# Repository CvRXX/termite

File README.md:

# Termite Devboard

Termite is an open source hardware devboard aimed at embedded library developers.

## Features
  * An stm32f103 cortex m3 microcontroller.
  * A protoboard space to mount components on.
  * An RGB led.
  * Support for lithium ion batteries as power source.
  * Charging of lithium ion batteries.
  * 128Kb of external onboard flash memory

## The idea
The idea came from my teacher who is developing multiple embedded libraries.
These libraries have support for many different types of displays, sensors, etc.
Everytime a change is made to the library my teacher had to hookup the sensors to an devboard. 
His wish was to have a devboard cheap enough he could solder the components on and leave them on.
This is what termite was designed for.

## Power
The board can be powered by 5v or 3.3 volt. 
There is a usb connector which can be used for power as well. 
Another option is to connect a lithium ion battery. 
If there is a voltage on the 5v rail a connected battery will be charged.

### WARNINGS about battery usage: 
  1. Only connect lithium ion batteries with a voltage of 3.7V marked on them.
  2. Don't connect batteries with a capacity less than 250mAh.
  3. Only connect batteries with an integrated protection circuit.
  4. Don't charge your board unattended. 

### Status leds:

| Green led  | Red led | Meaning |
| ------------- | ------------- | ------------- |
| Off  | Off  | No external power connected.
| On  | Off  | External power connected, battery full or not connected.
| On  | On  | External power connected, battery charging
| On  | Blinking  | External power connected, issue with battery detected.

## Flashing the microcontroller
The board include an IDC header that matches the pinout of the stlink-v2.
You need an IDC cable to connect between the flash tool and the board. 
After that it flashes just as any other stm microcontroller.

## Opening the files
To open the design files you need kicad. 
It's free software so you can just download it.

## Producing a board
If you want to produce a board you can export all the needed files from kicad.
It is hard (read impossible) to solder the battery charging chip with a normal soldering iron.
So if you want the battery charging you need to arrange for better equipment or arrange for pick and placing the board.

The board is 4 layer and can be produced by almost every common pcb factory.

If there are any problems I'm happy to help you on your way.
Just contact me!

## Testing the board
After production a testing script is available to check if the board is functioning oke. 
You can find the script and it's docs [here](https://github.com/CvRXX/termite-test-firmware).

## Examples with the termite board.
  * [A temperature sensor for painting scouting boats.](https://github.com/CvRXX/termite-demo)

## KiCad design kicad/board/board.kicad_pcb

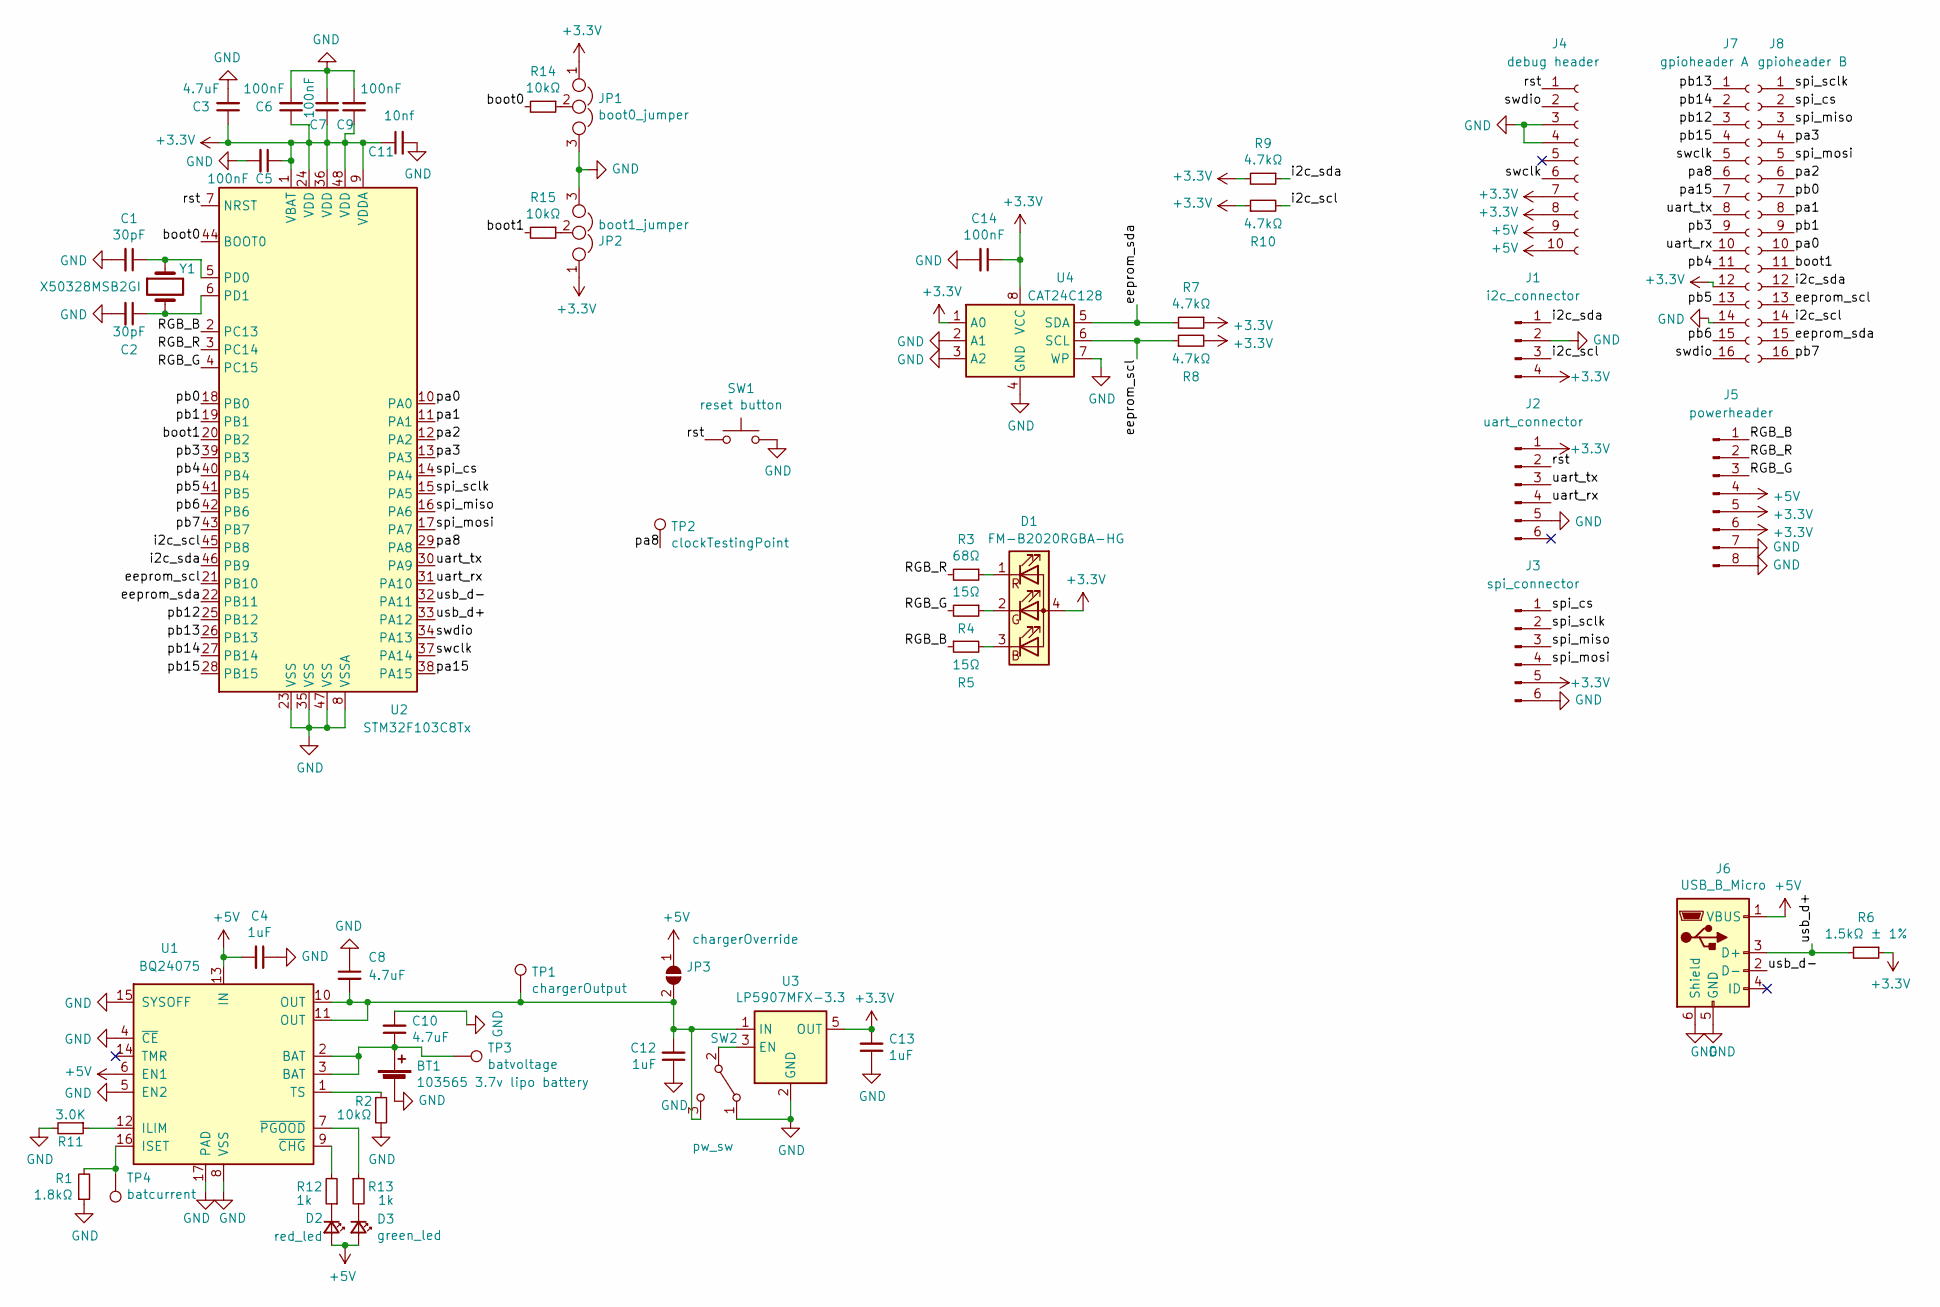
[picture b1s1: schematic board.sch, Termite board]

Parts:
BT1: 103565 3.7v lipo battery; PinHeader_1x02_P2.54mm_Vertical; LCSC C152154
C1, C2: 30pF; C_0402_1005Metric; LCSC C1570
C3, C8, C10: 4.7uF; C_0603_1608Metric; LCSC C19666
C4, C12, C13: 1uF; C_1206_3216Metric; LCSC C1848
C5, C6, C7, C9, C14: 100nF; C_0402_1005Metric; LCSC C1525
C11: 10nf; C_0603_1608Metric; LCSC C57112
D1: FM-B2020RGBA-HG; LCSC C108793
D2: red_led; LED_0603_1608Metric; LCSC C2286
D3: green_led; LED_0603_1608Metric; LCSC C72043
J1: i2c_connector; PinHeader_1x04_P2.54mm_Vertical; LCSC C124378
J2: uart_connector; PinSocket_1x06_P2.54mm_Horizontal; LCSC C225514
J3: spi_connector; PinHeader_1x06_P2.54mm_Vertical; LCSC C492405
J4: debug header; IDC-Header_2x05_P2.54mm_Vertical; LCSC C5665
J5: powerheader; PinHeader_1x08_P2.54mm_Vertical; LCSC C124381
J6: USB_B_Micro; AMPHENOL_10118194-0001LF; LCSC C132563
J7: gpioheader A; PinSocket_2x08_P2.54mm_Vertical
J8: gpioheader B; PinSocket_2x08_P2.54mm_Vertical
JP1: boot0_jumper; PinHeader_1x03_P2.54mm_Vertical; LCSC C49257
JP2: boot1_jumper; PinHeader_1x03_P2.54mm_Vertical; LCSC C49257
JP3: chargerOverride; SolderJumper-2_P1.3mm_Open_Pad1.0x1.5mm
R1: 1.8kΩ; R_0603_1608Metric_Pad0.98x0.95mm_HandSolder; LCSC C4177
R2, R14, R15: 10kΩ; R_0402_1005Metric; LCSC C25744
R3: 68Ω; R_0402_1005Metric; LCSC C25131
R4, R5: 15Ω; R_0402_1005Metric; LCSC C25083
R6: 1.5kΩ ± 1%; R_0402_1005Metric; LCSC C98835
R7, R8, R9, R10: 4.7kΩ; R_0402_1005Metric; LCSC C25900
R11: 3.0K; R_0603_1608Metric_Pad0.98x0.95mm_HandSolder; LCSC C4211
R12, R13: 1k; R_0402_1005Metric; LCSC C11702
SW1: reset button; K2-6639DP-E4SW-04; LCSC C223748
SW2: pw_sw; K301235D; LCSC C223839
TP1: chargerOutput; TestPoint_Pad_D1.0mm
TP2: clockTestingPoint; TestPoint_Pad_D1.0mm
TP3: batvoltage; TestPoint_Pad_D1.0mm
TP4: batcurrent; TestPoint_Pad_D1.0mm
U1: BQ24075; QFN-16-1EP_3x3mm_P0.5mm_EP1.7x1.7mm; LCSC C15464
U2: STM32F103C8Tx; LQFP-48_7x7mm_P0.5mm; LCSC C8304
U3: LP5907MFX-3.3; SOT-23-5; LCSC C80670
U4: CAT24C128; SOIC-8_3.9x4.9mm_P1.27mm; LCSC C81195
Y1: X50328MSB2GI; Crystal_SMD_5032-2Pin_5.0x3.2mm; LCSC C115962

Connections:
+3V3: C3.1, C5.1, C6.1, C7.1, C9.1, C11.1, C13.2, C14.1, D1.4 (A), J1.4, J2.1, J3.5, J4.7, J4.8, J5.5, J5.6, J7.12, JP1.1, JP2.1, R6.1, R7.1, R8.2, R9.2, R10.1, U2.1 (VBAT), U2.9 (VDDA), U2.24 (VDD), U2.36 (VDD), U2.48 (VDD), U3.5 (OUT), U4.1 (A0), U4.8 (VCC)
+5V: C4.2, D2.2 (A), D3.2 (A), J4.9, J4.10, J5.4, J6.1 (VBUS), JP3.1 (A), U1.6 (EN1), U1.13 (IN)
/RGB_B: J5.1, R5.1, U2.2 (PC13)
/RGB_G: J5.3, R4.2, U2.4 (PC15)
/RGB_R: J5.2, R3.2, U2.3 (PC14)
/boot0: R14.2, U2.44 (BOOT0)
/boot1: J8.11, R15.2, U2.20 (PB2)
/eeprom_scl: J8.13, R8.1, U2.21 (PB10), U4.6 (SCL)
/eeprom_sda: J8.15, R7.2, U2.22 (PB11), U4.5 (SDA)
/i2c_scl: J1.3, J8.14, R10.2, U2.45 (PB8)
/i2c_sda: J1.1, J8.12, R9.1, U2.46 (PB9)
/pa0: J8.10, U2.10 (PA0)
/pa1: J8.8, U2.11 (PA1)
/pa2: J8.6, U2.12 (PA2)
/pa3: J8.4, U2.13 (PA3)
/pa8: J7.6, TP2.1, U2.29 (PA8)
/pa15: J7.7, U2.38 (PA15)
/pb0: J8.7, U2.18 (PB0)
/pb1: J8.9, U2.19 (PB1)
/pb3: J7.9, U2.39 (PB3)
/pb4: J7.11, U2.40 (PB4)
/pb5: J7.13, U2.41 (PB5)
/pb6: J7.15, U2.42 (PB6)
/pb7: J8.16, U2.43 (PB7)
/pb12: J7.3, U2.25 (PB12)
/pb13: J7.1, U2.26 (PB13)
/pb14: J7.2, U2.27 (PB14)
/pb15: J7.4, U2.28 (PB15)
/rst: J2.2, J4.1, SW1.1, U2.7 (NRST)
/spi_cs: J3.1, J8.2, U2.14 (PA4)
/spi_miso: J3.3, J8.3, U2.16 (PA6)
/spi_mosi: J3.4, J8.5, U2.17 (PA7)
/spi_sclk: J3.2, J8.1, U2.15 (PA5)
/swclk: J4.6, J7.5, U2.37 (PA14)
/swdio: J4.2, J7.16, U2.34 (PA13)
/uart_rx: J2.4, J7.10, U2.31 (PA10)
/uart_tx: J2.3, J7.8, U2.30 (PA9)
/usb_d+: J6.3 (D+), R6.2, U2.33 (PA12)
/usb_d-: J6.2 (D-), U2.32 (PA11)
GND: BT1.2 (-), C1.2, C2.2, C3.2, C4.1, C5.2, C6.2, C7.2, C8.1, C9.2, C10.2, C11.2, C12.1, C13.1, C14.2, J1.2, J2.5, J3.6, J4.3, J4.4, J5.7, J5.8, J6.5 (GND), J6.6 (Shield), J7.14, JP1.3, JP2.3, R1.1, R2.2, R11.2, SW1.2, SW2.1 (A), U1.4 (~CE), U1.5 (EN2), U1.8 (VSS), U1.15 (SYSOFF), U1.17 (PAD), U2.8 (VSSA), U2.23 (VSS), U2.35 (VSS), U2.47 (VSS), U3.2 (GND), U4.2 (A1), U4.3 (A2), U4.4 (GND), U4.7 (WP)
unnamed: BT1.1 (+), C10.1, TP3.1, U1.2 (BAT), U1.3 (BAT)
unnamed: C1.1, U2.5 (PD0), Y1.1
unnamed: C2.1, U2.6 (PD1), Y1.2
unnamed: C8.2, C12.2, JP3.2 (B), SW2.3 (C), TP1.1, U1.10 (OUT), U1.11 (OUT), U3.1 (IN)
unnamed: D1.1 (RK), R3.1
unnamed: D1.2 (GK), R4.1
unnamed: D1.3 (BK), R5.2
unnamed: D2.1 (K), R12.1
unnamed: D3.1 (K), R13.2
unnamed: JP1.2, R14.1
unnamed: JP2.2, R15.1
unnamed: R1.2, TP4.1, U1.16 (ISET)
unnamed: R2.1, U1.1 (TS)
unnamed: R11.1, U1.12 (ILIM)
unnamed: R12.2, U1.9 (~CHG)
unnamed: R13.1, U1.7 (~PGOOD)
unnamed: SW2.2 (B), U3.3 (EN)

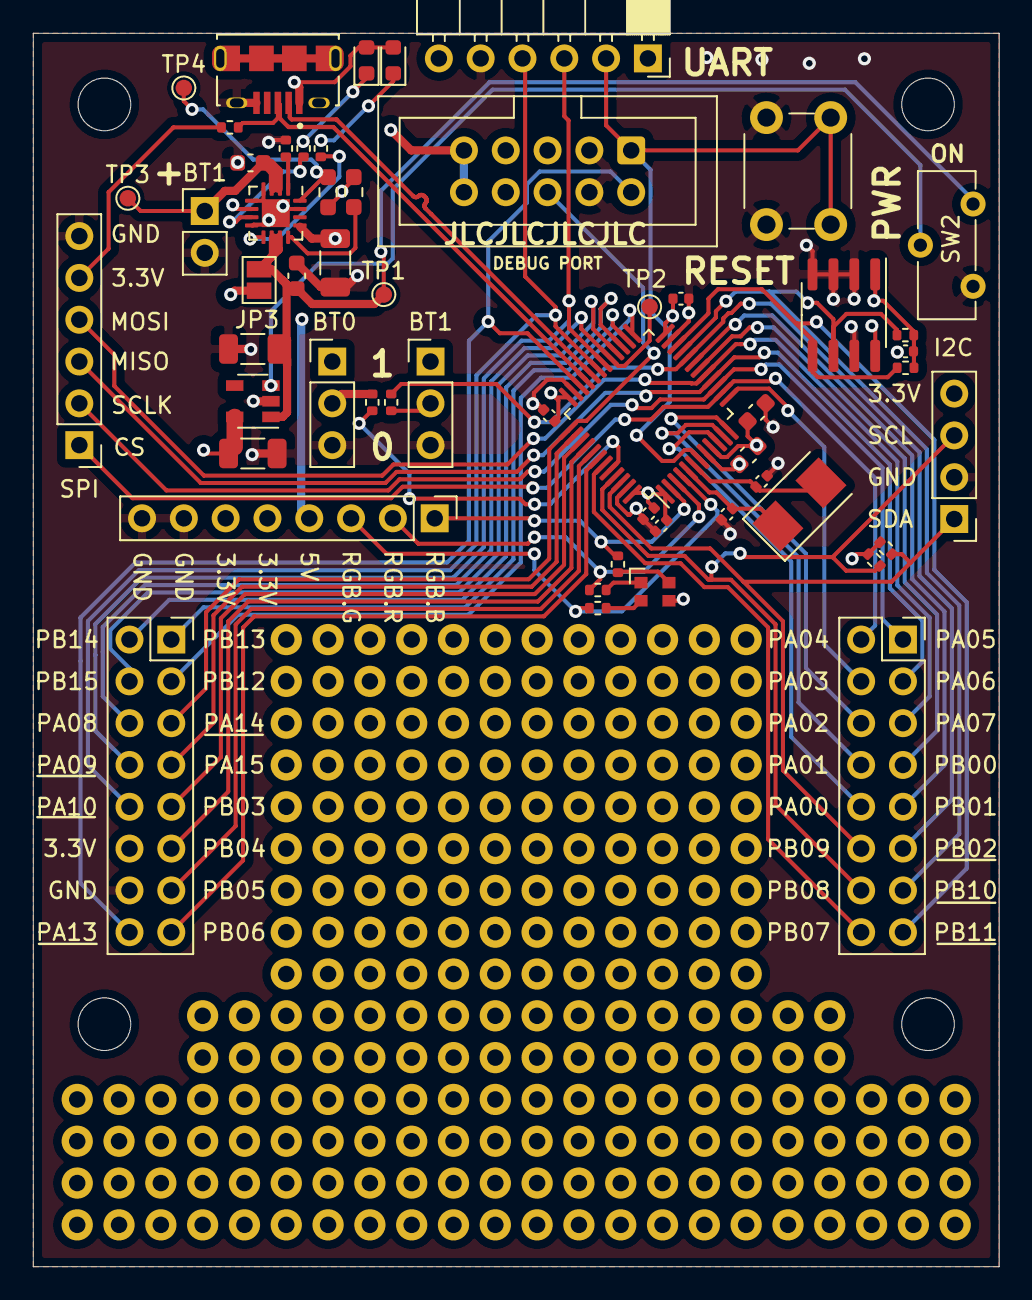
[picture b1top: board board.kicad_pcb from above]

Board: 4 copper layers, 58.7 x 74.9 mm, 55 parts (0 on the bottom side), 57 nets.

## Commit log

2020-10-31 initial version
2020-11-25 fixing #6
2021-01-06 v1.1 adding
2021-01-10 putting the thermistor replacement resistor to gnd instead of 5v fixing #18
2021-01-10 adding labeling for uart fixing #12
2021-01-10 adding labeling for the power switch
2021-01-10 adding polarity marking for bat connector fixing #14
2021-01-10 adding special markings for pins that cant be made an normal output fixing #19
2021-01-10 adding special markings for uart for #19
2021-01-11 adding testpoint to measure bat charge current This will make it easier to identify bat charging problems.
2021-01-16 changing crystal for a 8MHz one instead of 16MHz
2021-01-16 making the leds less bright by replacing r12 and r13 for 1k fixing #16
2021-01-19 rewired the usb bus so the impedence is matched for JLC7628 fixing #20
2021-01-19 adding termite logo to back of pcb fixing #10
2021-01-26 adding licence and readme
